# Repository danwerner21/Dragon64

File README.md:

(note that I need to get a better picture of the screen, this is s-video and is very clear in person)

# Dragon 64 Clone PCB

The Dragon 64 is a home computer that was built in the 1980s for the European market by Dragon Data, Ltd. The Dragons are very similar to the TRS-80 Color Computer, and in fact provisions have been made to allow the keyboard to become compatible with a TRS-80 color computer clone.   This version of the Dragon 64 computer produces NTSC rather than PAL composite video and has the ability to produce "Commodore style LCA" s-video output for a much clearer video display.  It also supports either a vertical or horizontal cartridge slot and TTL level serial capabilities for convenient use of modern TTL to USB adaptors.

It should be possible for this PCB to become a Tandy Color Computer clone as well, but this is not implimented in V1.

A regulated 12V and 5V power supply is required.

The main PCB also includes a DragonDOS floppy controller that can be optionally populated to support floppy disk support.

A design is included for a 3d-printed retro style case.

Note that much of this work is based on the work done by Ciaran Anscomb.  Without that original work, this would have taken much longer to complete.

More generalized information on this line of retro computers can be found here:

   * https://en.wikipedia.org/wiki/Dragon_32/64
   * https://colorcomputerarchive.com/
   * https://cococentral.com/
   * https://www.6809.org.uk/dragon/
   * http://dragondata.co.uk/

---

## To Do:
* test the joystick interface
* test the cassette interface
* test the printer interface
---

## What is included in this repo?
As of this time, the repo includes

1. The Mainboard PCB Kicad design and Gerber files
2. The Keyboard PCB Kicad design and Gerber files
3. OpenSCAD and STL files for a 3d printed case
4. SVG file for custom keycaps from MAX Keyboard

---

## Known Bugs

### System Jumpers
LK1 - Ram Size Selection 64K=1&2, 32K=2&3

J3 - Composite on Luma J3 on for composite video, off for S-video

J5 - Enable Disk ROM

---

## Bill Of Materials

### Mainboard
QTY|ref|value|part|description
--------|--------|----|--------|--------
1|IC4|4050|4050|
1|IC7|4069|4069|Hex inverter
8|IC15, IC16, IC21, IC22, IC26, IC27, IC32, IC33|4164|4164|
1|IC6|4529|4529|
1|IC11|6551|6551|
2|IC5,IC8|6821|6821|Peripheral Interface Adapter 1MHz| DIP-40
1|IC10|6847|6847|
1|IC39|6883|6883|
1|D8|1N914|1N914|100V 0.3A Small Signal Fast Switching Diode| DO-35
2|IC34,IC37|27C128|27C128|OTP EPROM 128 KiBit| [Obsolete 2004-01]
1|U5|27C64|27C64|OTP EPROM 64 KiBit| [Obsolete 2004-01]
2|IC35,U3|74LS00|74LS00|quad 2-input NAND gate
1|IC36|74LS02|74LS02|quad 2-input NOR gate
1|U6|74LS04|74LS04|Hex Inverter
1|U8|74LS06N|74LS06N|Inverter Open Collect
1|U4|74LS07|74LS07|Hex Buffers and Drivers With Open Collector High Voltage Outputs
1|IC40|74LS138|74LS138|Decoder 3 to 8 active low outputs
1|U7|74LS139|74LS139|Dual Decoder 1 of 4| Active low outputs
1|U9|74LS174|74LS174|Hex D-type Flip-Flop| reset
2|IC1|,C25|74LS244|74LS244|Octal Buffer and Line Driver With 3-State Output| active-low enables| non-inverting outputs
1|IC20|74LS273|74LS273|8-bit D Flip-Flop| reset
1|J1|Screw Terminal|5mm pitch|Power supply
1|C3|.002u|C|Unpolarized capacitor
37|C1, C7, C11, C12, C18, C20, C21, C22, C29, C31, C32, C34, C38, C39, C40, C41, C42, C43, C45, C46, C47, C50, C51, C52, C53, C55, C56, C57, C62, C65, C66, C70, C71, C72, C73, C74, C75, C76|.01u|C|Unpolarized capacitor
5|C6,C13,C14,C15,C16|.02u|C|Unpolarized capacitor
7|C27, C33, C4, C49, C59, C60, C61|.1u|C|Unpolarized capacitor
2|C33,C49|0.1uf|C|Unpolarized capacitor
1|C2|0.22uf|C|Unpolarized capacitor
1|C37|100pf|C|Unpolarized capacitor
1|C78|10nf|C|Unpolarized capacitor
2|C8,C48|1u|C|Unpolarized capacitor
1|C17|22p|C|Unpolarized capacitor
1|C35|25uf|C|Unpolarized capacitor
1|C44|470pf|C|Unpolarized capacitor
1|C67|47p|C|Unpolarized capacitor
1|C30|56pf|C|Unpolarized capacitor
1|C10|10u|C_Polarized_Small_US|Polarized capacitor| small US symbol
4|C9,C24,C25,C54|1u|C_Polarized_Small_US|Polarized capacitor| small US symbol
1|C26|C63|100uf|C_Polarized_US|Polarized capacitor| US symbol
1|C19|10uf|C_Polarized_US|Polarized capacitor| US symbol
1|C23|10uf 16v|C_Polarized_US|Polarized capacitor| US symbol
2|C58,C64|4.7uf|C_Polarized_US|Polarized capacitor| US symbol
1|C36|47uf|C_Polarized_US|Polarized capacitor| US symbol
2|C11,C7|.01u|C_Small|Unpolarized capacitor| small symbol
1|C77|8-70pf|C_Trim|Trimmable capacitor
1|J3|composite on luma|Conn_01x02_Male|Generic connector| single row| 01x02| script generated (kicad-library-utils/schlib/autogen/connector/)
1|J5|DISK ROM ENABLE|Conn_01x02_Male|Generic connector| single row| 01x02| script generated (kicad-library-utils/schlib/autogen/connector/)
1|J2|TTL Serial Connector|Conn_01x06_Male|Generic connector| single row| 01x06| script generated (kicad-library-utils/schlib/autogen/connector/)
1|PL6|Power/Video|Conn_01x09|Generic connector| single row| 01x09| script generated (kicad-library-utils/schlib/autogen/connector/)
1|PL1|Keyboard|Conn_01x16|Generic connector| single row| 01x16| script generated (kicad-library-utils/schlib/autogen/connector/)
1|PL2|Printer|Conn_02x10_Odd_Even|Generic connector| double row| 02x10| odd/even pin numbering scheme (row 1 odd numbers| row 2 even numbers)| script generated (kicad-library-utils/schlib/autogen/connector/)
1|J6|Floppy Interface|Conn_02x17_Odd_Even|Generic connector| double row| 02x17| odd/even pin numbering scheme (row 1 odd numbers| row 2 even numbers)| script generated (kicad-library-utils/schlib/autogen/connector/)
1|PL7|Cartridge|Conn_02x20_Odd_Even|Generic connector| double row| 02x20| odd/even pin numbering scheme (row 1 odd numbers| row 2 even numbers)| script generated (kicad-library-utils/schlib/autogen/connector/)
1|Y2|1.8432Mhz|Crystal|Two pin crystal
1|X1|14.31818Mhz|CXO_DIP14|Crystal Clock Oscillator| DIP14-style metal package
1|D4|1N4002|D|Diode
4|D5,D6,D7,D11|1N4148|D|Diode
4|D1,D12,D13,D14|1N914|D|Diode
2|D2,D3|BZX 61|D_Zener_Small|Zener diode| small symbol
1|J4|DB9_Male|DB9_Male|9-pin male D-SUB connector
1|PL4|Cassette|DIN-5_180degree|5-pin DIN connector (5-pin DIN-5 stereo)
2|PL3,PL5|Joystick L|DIN-6|6-pin DIN connector
1|LK1|Jumper_3_Bridged12| pins 1+2 closed/bridged
4|L1,L2,L3,L4|3.3u|L|Inductor
1|IC2|LM393|LM393|Low-Power| Low-Offset Voltage| Dual Comparators| DIP-8/SOIC-8/TO-99-8
1|U1|MAX232|MAX232|Dual RS232 driver/receiver| 5V supply| 120kb/s| 0C-70C
1|U2|MC1372|MC1372|
1|IC38|MC6809E|MC6809E|
2|Q2,Q3|2N2222|Q_NPN_BCE|NPN transistor| base/collector/emitter
1|TR1|BC182L|Q_NPN_BCE|NPN transistor| base/collector/emitter
1|Q1|BC557|Q_PNP_BCE|PNP transistor| base/collector/emitter
4|R45,R46,R47,R48|150|R|Resistor
2|R7,R12|390|R|Resistor
1|R30|420|R|Resistor
3|R6,R31,R85|470|R|Resistor
1|R43|750|R|Resistor
1|R13|820|R|Resistor
3|R17,R32,R42|100K|R|Resistor
1|R1|100R|R|Resistor
6|R9,R11,R15,R16,R26,R28|10K|R|Resistor
1|R29|10M|R|Resistor
1|R23|15K|R|Resistor
6|R10,R18,R27,R41,R44,R64|1K|R|Resistor
1|R22|1M5|R|Resistor
1|R4|220R|R|Resistor
11|R73,R74,R75,R76,R77 ,R78,R79,R80,R81,R82,R83|22R|R|Resistor
1|R40|33K|R|Resistor
1|R3|470R|R|Resistor
11|R14,R2,R24,R25,R65 ,R66,R67,R68,R69,R70,R71|4K7|R|Resistor
1|R8|5.6k|R|Resistor
2|R20,R21|56K|R|Resistor
1|R39|68K|R|Resistor
1|R19|6K8|R|Resistor
1|R5|8K2|R|Resistor
2|RV1,RV2|10K-Read|R_Potentiometer_Trim|Trim-potentiometer
1|R38|10K 1%|R_Small|Resistor| small symbol
1|R33|160K|R_Small|Resistor| small symbol
1|R37|20K 1%|R_Small|Resistor| small symbol
1|R34|330K|R_Small|Resistor| small symbol
1|R36|40K2 1%|R_Small|Resistor| small symbol
1|R35|80K6 1%|R_Small|Resistor| small symbol
1|RLA1|SPDT|TIANBO-HJR-4102-L|TIANBO HJR-4102-L| Single Pole Relay| 5mm Pitch| 3A
1|U10|WD2797|WD2797|Floppy disk controller| DIP-40
1|X2|1Mhz|XO91|HCMOS Clock Oscillator

### Keyboard
QTY|ref|value|part|description
--------|--------|----|--------|--------
53|SW(X)|KEYSWITCH|MX Cherry - Linear
3||Switch Leveling Kit|LEVELING KIT FOR LARGER KEYS|EXAMPLE:https://www.amazon.com/Keyboard-Screw-Stabilizers-6-25u-Mechanical/dp/B094R45K8Z  -or-   https://www.amazon.com/dp/B0978PWJG9 
1||Switch Leveling Kit|LEVELING KIT FOR SPACEBAR| EXAMPLE:https://www.amazon.com/Keyboard-Screw-Stabilizers-6-25u-Mechanical/dp/B094R45K8Z  -or-   https://www.amazon.com/dp/B0978PWJG9 
2|J1,J2|01X16 HEADER|Connector_PinHeader_2.54mm:PinHeader_1x16_P2.54mm_Vertical

### Floppy Drive Calibration (an oscilloscope is required)
1. power on, allow machine to reset and boot

2. ground Pin 22 of U10(WD2797)

3. Set VC0 by Measuring at pin 16 of the U10(WD2797),  Adjust the signal to 250 KHz (capacitor C77)

4. WP setting by Measuring signal at pin 31 of the U10(WD2797), Set pulse width to 300ns (RV2 potentiometer)

5. PR adjustment by Measuring signal at pin 29 of U10(WD2797), Set pulse width to 600ns (potentiometer RV1)

6. remove Pin 22 of the U10(WD2797) from ground

7. restart machine

### Case

### Questions?

If there are any questions, I can be reached at vic2020Dan at gmail dot com.

---

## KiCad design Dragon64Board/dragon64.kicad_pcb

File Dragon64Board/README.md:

# Dragon 64 schematic

... and PCB layout, in [KiCad](https://www.kicad.org/).

The schematic capture is complete, and I've done one full verification pass.
But I'm still making no promises about correctness!  I've uploaded a PDF for
those without access to KiCad.

 * [Dragon 64 schematic PDF](https://www.6809.org.uk/dragon/dragon64-schematic.pdf)

A lot of the PCB positioning is now correct - at least to the nearest mm,
usually better - and everything's pointing in a sensible direction with the
exception of some diodes: Dragon Data ensured they always had the cathode to
the right, presumably to avoid manufacturing confusion, and I've preserved that
decision.

As it stands the PCB is now fully routed.  I think it has reasonable power
distribution, and where possible, I've tried to route such that the decoupling
capacitor positions make sense.  Crystal tracks should be reasonably well
separated from anything else, and apart from a tiny skirt around the outside of
the ACIA crystal housing, no tracks pass underneath them either.

[Freerouting](https://github.com/freerouting/freerouting) did the rest, and it
looks ok to me!  Less than 200 vias in the end.  Fully autorouted achieves a
lot less, but I wasn't terribly happy with how it dealt with the sensitive bits
above.  I think 200 still compares pretty well to the original boards.

It would be nice to learn some FreeCAD to make the 3D view nicer, but
I must admit that's looking pretty low priority for now.

 * [3D view](https://www.6809.org.uk/dragon/dragon64-kicad-pcb.jpg)

Changes from the original:

 * The 240° 5-pin DIN sockets used for joysticks appear to be a bit harder to
   find now.  I've replaced them with (compatible) 6-pin sockets.
 * The footprint for the 7-pin DIN serial connector is incompatible (2-3-2
   instead of 3-4).  This reflects what I've found to be available today.
 * Two more inductors and capacitors have been added as optional components to
   enable the second firebutton on CoCo 3 compatible joysticks.

Note also that the mounting holes for the edge connector are placed
differently, and not very well with respect to the board, so definitely don't
use this layout as-is.  40-way 2.54mm pitch card edge connector sockets seem to
be like hen's teeth at the moment.  Stewart Orchard points out that EDAC list
some, and that's the footprint you currently see.  Not that anyone appears to
sell it.  Likely I'll update the footprint to match what's in our Dragons so
that if anyone's fool enough to get a board made, they can take a donor.

## Acknowledgements

Thanks to Richard Harding for hosting high quality copies of the original
drawings - doing this from the old scans would have been nigh on impossible.

 * [Original drawings](http://dragondata.co.uk/tech/circuit-diag/index.html)

Thanks also to Stewart Orchard, who has done a similar capture of the Dragon's
PSU board.  I also nabbed his 3D model of the DIN socket to represent all the
similar ports in this project (you'll notice they're the wrong shape for the
joystick ports, and none of them have more than three pins).

 * [DragonISS4PSU](https://gitlab.com/sorchard001/dragoniss4psu)

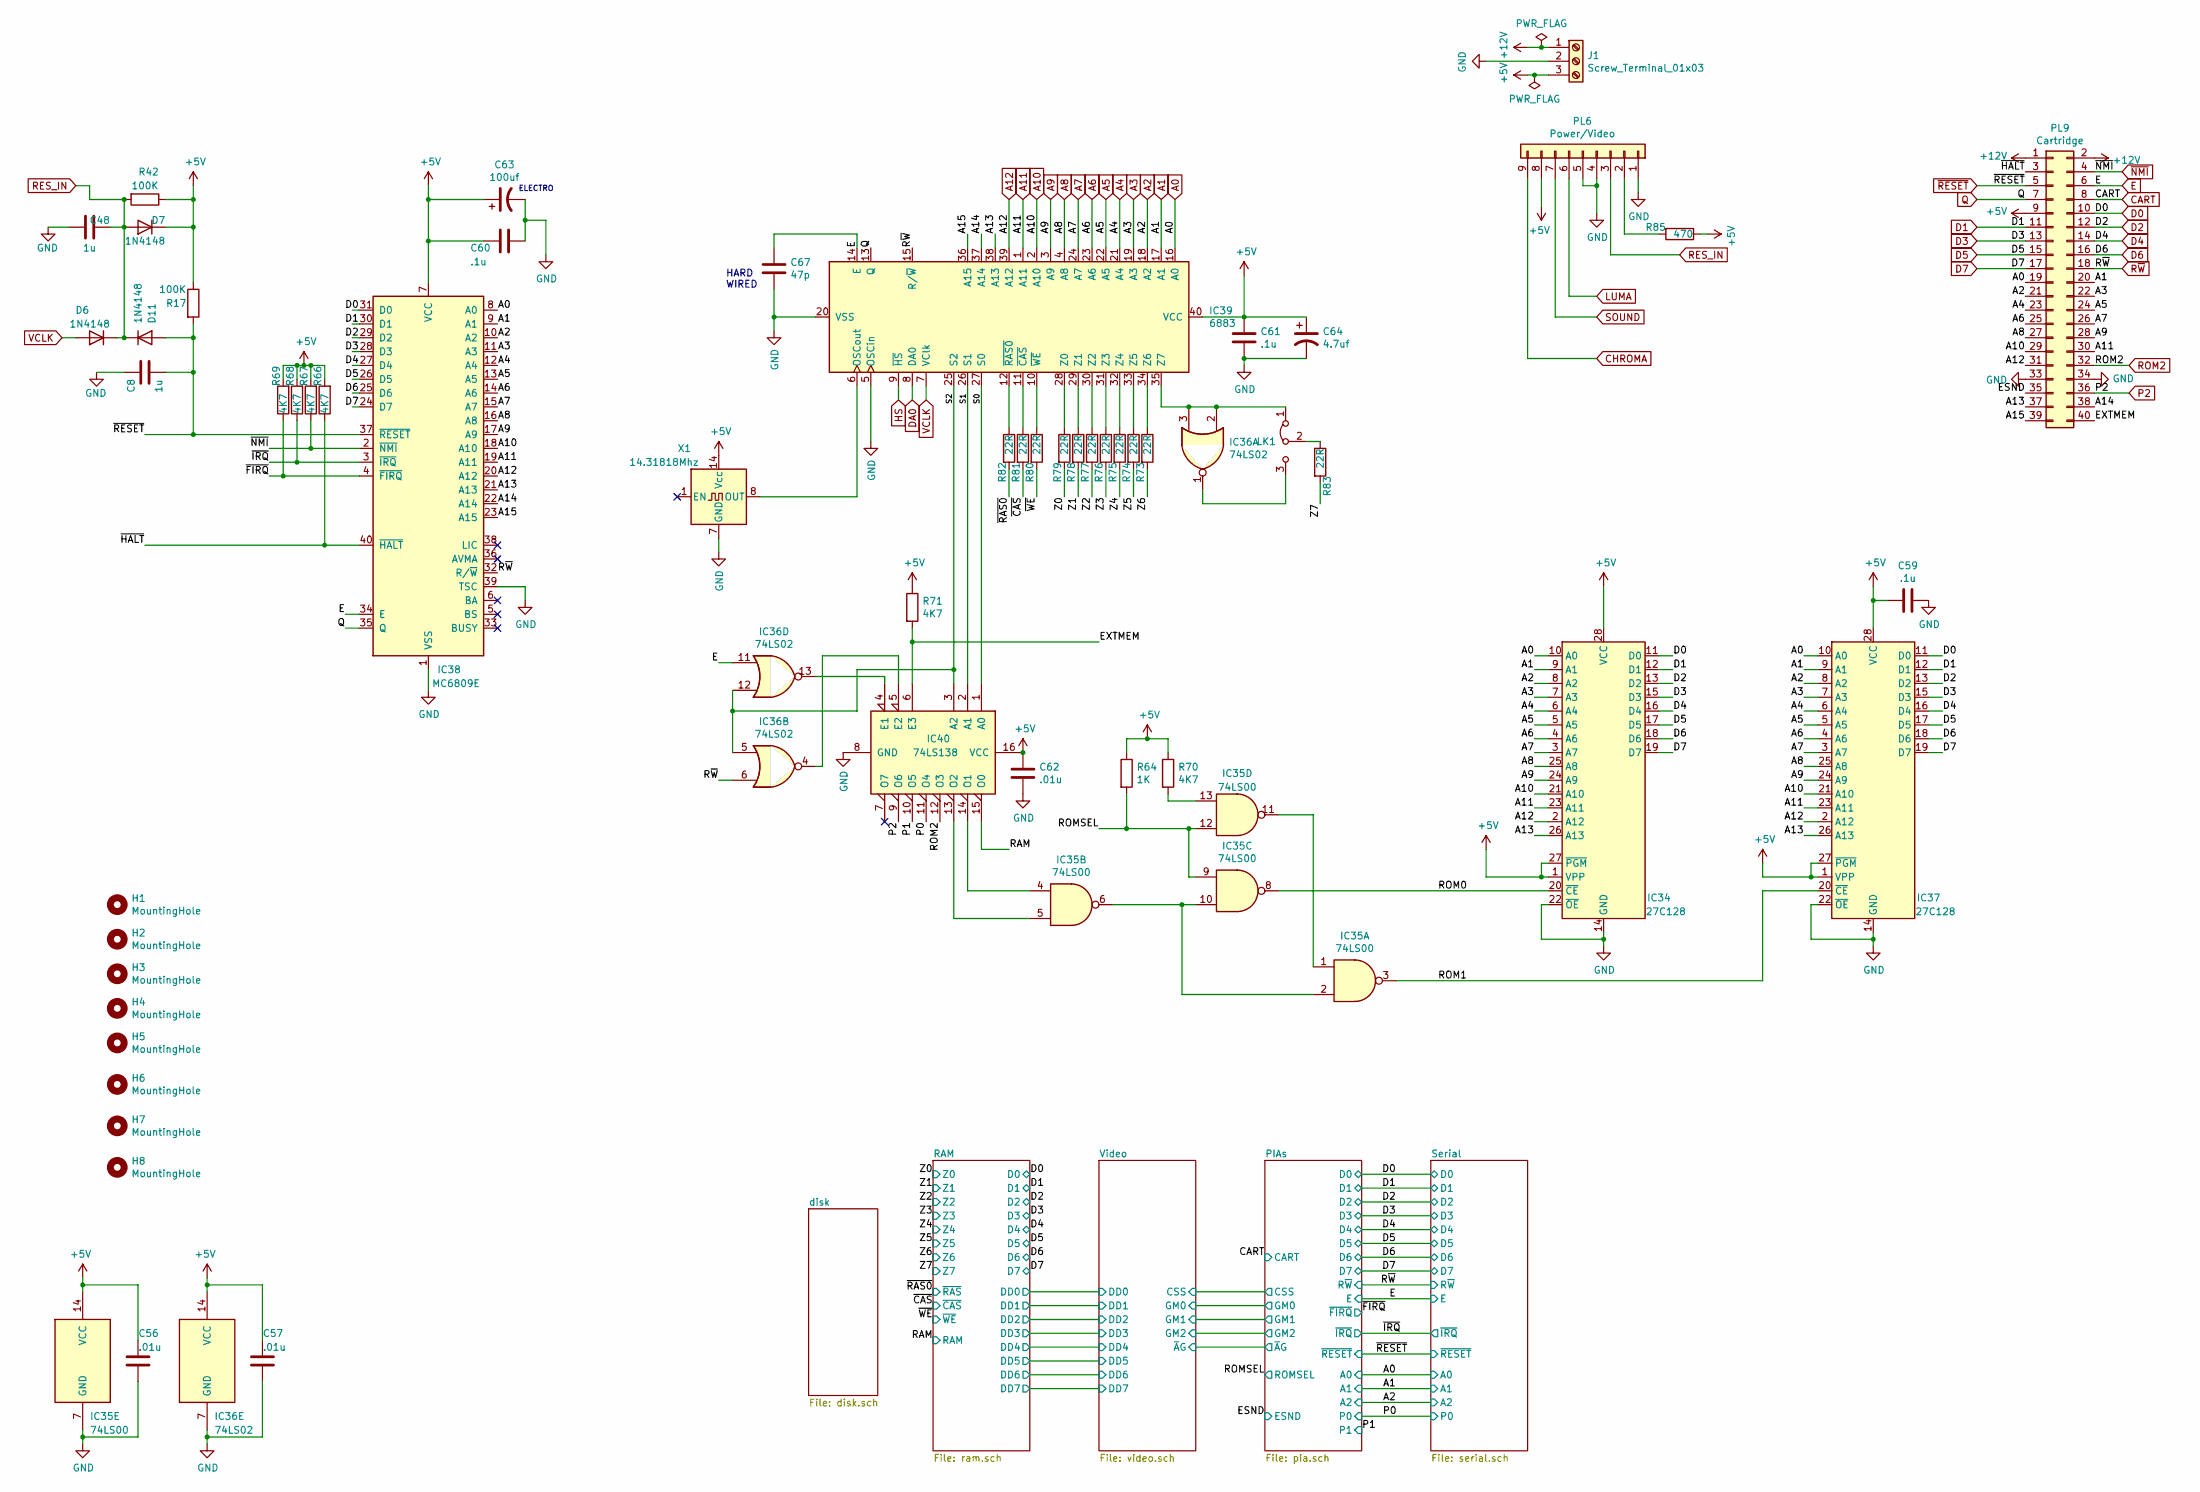
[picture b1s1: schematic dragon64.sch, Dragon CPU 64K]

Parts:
C8, C48: 1u; C_Disc_D7.5mm_W2.5mm_P5.00mm
C56, C57, C62: .01u; C_Disc_D7.5mm_W2.5mm_P5.00mm
C59, C60, C61: .1u; C_Disc_D7.5mm_W2.5mm_P5.00mm
C63: 100uf; CP_Radial_D4.0mm_P2.00mm
C64: 4.7uf; CP_Radial_D4.0mm_P2.00mm
C67: 47p; C_Disc_D7.5mm_W2.5mm_P5.00mm
D6, D7, D11: 1N4148; D_DO-35_SOD27_P7.62mm_Horizontal
H1, H2, H3, H4, H5, H6, H7, H8: MountingHole; MountingHole_3.2mm_M3
IC34, IC37: 27C128; DIP-28_W15.24mm_Socket_LongPads
IC35: 74LS00; DIP-14_W7.62mm_Socket_LongPads
IC36: 74LS02; DIP-14_W7.62mm_Socket_LongPads
IC38: MC6809E; DIP-40_W15.24mm_Socket_LongPads
IC39: 6883; DIP-40_W15.24mm_Socket_LongPads
IC40: 74LS138; DIP-16_W7.62mm_Socket_LongPads
J1: Screw_Terminal_01x03; TerminalBlock_RND_205-00277_1x03_P5.00mm_Vertical
LK1: PinHeader_1x03_P2.54mm_Vertical
PL6: Power/Video; PinHeader_1x09_P2.54mm_Vertical
PL9: Cartridge; Edge_2x20_P2.54mm_Horizontal
R17, R42: 100K; R_Axial_DIN0207_L6.3mm_D2.5mm_P7.62mm_Horizontal
R64: 1K; R_Axial_DIN0207_L6.3mm_D2.5mm_P7.62mm_Horizontal
R66, R67, R68, R69, R70, R71: 4K7; R_Axial_DIN0207_L6.3mm_D2.5mm_P7.62mm_Horizontal
R73, R74, R75, R76, R77, R78, R79, R80, R81, R82, R83: 22R; R_Axial_DIN0207_L6.3mm_D2.5mm_P7.62mm_Horizontal
R85: 470; R_Axial_DIN0207_L6.3mm_D2.5mm_P7.62mm_Horizontal
X1: 14.31818Mhz; DIP-14_W7.62mm_Socket_LongPads

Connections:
+5V: C56.1, C57.1, C59.2, C60.2, C61.2, C62.1, C63.1, C64.1, D7.1 (K), IC34.1 (VPP), IC34.27 (~PGM), IC34.28 (VCC), IC35.14 (VCC), IC36.14 (VCC), IC37.1 (VPP), IC37.27 (~PGM), IC37.28 (VCC), IC38.7 (VCC), IC39.40 (VCC), IC40.16 (VCC), J1.3, PL6.8, PL9.9, R17.1, R42.1, R64.1, R66.2, R67.2, R68.2, R69.2, R70.1, R71.1, R85.1, X1.14 (Vcc); also elsewhere on the board
+12V: J1.1, PL9.1, PL9.2; also elsewhere on the board
/A13: IC34.26 (A13), IC37.26 (A13), IC38.21 (A13), IC39.38 (A13), PL9.37
/A14: IC38.22 (A14), IC39.37 (A14), PL9.38
/A15: IC38.23 (A15), IC39.36 (A15), PL9.39
/ESND: PL9.35; also elsewhere on the board
/EXTMEM: IC40.6 (E3), PL9.40, R71.2
/P0: IC40.11 (O4); also elsewhere on the board
/P1: IC40.10 (O5); also elsewhere on the board
/RAM: IC40.15 (O0); also elsewhere on the board
/ROM0: IC34.20 (~CE), IC35.8
/ROM1: IC35.3, IC37.20 (~CE)
/ROMSEL: IC35.9, IC35.12, R64.2; also elsewhere on the board
/S0: IC39.27 (S0), IC40.1 (A0)
/S1: IC39.26 (S1), IC40.2 (A1)
/S2: IC36.5, IC36.12, IC39.25 (S2), IC40.3 (A2)
/Z0: R79.2; also elsewhere on the board
/Z1: R78.2; also elsewhere on the board
/Z2: R77.2; also elsewhere on the board
/Z3: R76.2; also elsewhere on the board
/Z4: R75.2; also elsewhere on the board
/Z5: R74.2; also elsewhere on the board
/Z6: R73.2; also elsewhere on the board
/Z7: R83.2; also elsewhere on the board
/~CAS: R81.2; also elsewhere on the board
/~FIRQ: IC38.4 (~FIRQ), R69.1; also elsewhere on the board
/~HALT: IC38.40 (~HALT), PL9.3, R66.1
/~IRQ: IC38.3 (~IRQ), R68.1; also elsewhere on the board
/~RAS0: R82.2; also elsewhere on the board
/~WE: R80.2; also elsewhere on the board
A0: IC34.10 (A0), IC37.10 (A0), IC38.8 (A0), IC39.16 (A0), PL9.19; also elsewhere on the board
A1: IC34.9 (A1), IC37.9 (A1), IC38.9 (A1), IC39.17 (A1), PL9.20; also elsewhere on the board
A2: IC34.8 (A2), IC37.8 (A2), IC38.10 (A2), IC39.18 (A2), PL9.21; also elsewhere on the board
A3: IC34.7 (A3), IC37.7 (A3), IC38.11 (A3), IC39.19 (A3), PL9.22; also elsewhere on the board
A4: IC34.6 (A4), IC37.6 (A4), IC38.12 (A4), IC39.21 (A4), PL9.23; also elsewhere on the board
A5: IC34.5 (A5), IC37.5 (A5), IC38.13 (A5), IC39.22 (A5), PL9.24; also elsewhere on the board
A6: IC34.4 (A6), IC37.4 (A6), IC38.14 (A6), IC39.23 (A6), PL9.25; also elsewhere on the board
A7: IC34.3 (A7), IC37.3 (A7), IC38.15 (A7), IC39.24 (A7), PL9.26; also elsewhere on the board
A8: IC34.25 (A8), IC37.25 (A8), IC38.16 (A8), IC39.4 (A8), PL9.27; also elsewhere on the board
A9: IC34.24 (A9), IC37.24 (A9), IC38.17 (A9), IC39.3 (A9), PL9.28; also elsewhere on the board
A10: IC34.21 (A10), IC37.21 (A10), IC38.18 (A10), IC39.2 (A10), PL9.29; also elsewhere on the board
A11: IC34.23 (A11), IC37.23 (A11), IC38.19 (A11), IC39.1 (A11), PL9.30; also elsewhere on the board
A12: IC34.2 (A12), IC37.2 (A12), IC38.20 (A12), IC39.39 (A12), PL9.31; also elsewhere on the board
CART: PL9.8; also elsewhere on the board
CHROMA: PL6.9; also elsewhere on the board
D0: IC34.11 (D0), IC37.11 (D0), IC38.31 (D0), PL9.10; also elsewhere on the board
D1: IC34.12 (D1), IC37.12 (D1), IC38.30 (D1), PL9.11; also elsewhere on the board
D2: IC34.13 (D2), IC37.13 (D2), IC38.29 (D2), PL9.12; also elsewhere on the board
D3: IC34.15 (D3), IC37.15 (D3), IC38.28 (D3), PL9.13; also elsewhere on the board
D4: IC34.16 (D4), IC37.16 (D4), IC38.27 (D4), PL9.14; also elsewhere on the board
D5: IC34.17 (D5), IC37.17 (D5), IC38.26 (D5), PL9.15; also elsewhere on the board
D6: IC34.18 (D6), IC37.18 (D6), IC38.25 (D6), PL9.16; also elsewhere on the board
D7: IC34.19 (D7), IC37.19 (D7), IC38.24 (D7), PL9.17; also elsewhere on the board
DA0: IC39.8 (DA0); also elsewhere on the board
E: C67.2, IC36.11, IC38.34 (E), IC39.14 (E), PL9.6; also elsewhere on the board
GND: C8.1, C48.1, C56.2, C57.2, C59.1, C60.1, C61.1, C62.2, C63.2, C64.2, C67.1, IC34.14 (GND), IC34.22 (~OE), IC35.7 (GND), IC36.7 (GND), IC37.14 (GND), IC37.22 (~OE), IC38.1 (VSS), IC38.39 (TSC), IC39.5 (OSCin), IC39.20 (VSS), IC40.8 (GND), J1.2, PL6.1, PL6.4, PL6.5, PL9.33, PL9.34, X1.7 (GND); also elsewhere on the board
HS: IC39.9 (~HS~); also elsewhere on the board
LUMA: PL6.6; also elsewhere on the board
unnamed: IC35.1, IC35.11
unnamed: IC35.4, IC40.14 (O1)
unnamed: IC35.5, IC40.13 (O2)
unnamed: IC35.2, IC35.6, IC35.10
unnamed: IC35.13, R70.2
unnamed: IC36.1, LK1.3 (B)
unnamed: IC36.2, IC36.3, IC39.35 (Z7), LK1.1 (A)
unnamed: IC36.4, IC40.5 (E2)
unnamed: IC36.13, IC40.4 (E1)
unnamed: IC39.6 (OSCout), X1.8 (OUT)
unnamed: IC39.10 (~WE~), R80.1
unnamed: IC39.11 (~CAS~), R81.1
unnamed: IC39.12 (~RAS0~), R82.1
unnamed: IC39.28 (Z0), R79.1
unnamed: IC39.29 (Z1), R78.1
unnamed: IC39.30 (Z2), R77.1
unnamed: IC39.31 (Z3), R76.1
unnamed: IC39.32 (Z4), R75.1
unnamed: IC39.33 (Z5), R74.1
unnamed: IC39.34 (Z6), R73.1
unnamed: LK1.2 (C), R83.1
unnamed: PL6.2, R85.2
P2: IC40.9 (O6), PL9.36; also elsewhere on the board
Q: IC38.35 (Q), IC39.13 (Q), PL9.7; also elsewhere on the board
RES_IN: C48.2, D6.1 (K), D7.2 (A), D11.1 (K), PL6.3, R42.2
ROM2: IC40.12 (O3), PL9.32; also elsewhere on the board
R~W~: IC36.6, IC38.32 (R/~W), IC39.15 (R/~W~), PL9.18; also elsewhere on the board
SOUND: PL6.7; also elsewhere on the board
VCLK: D6.2 (A), IC39.7 (VClk); also elsewhere on the board
~NMI: IC38.2 (~NMI), PL9.4, R67.1; also elsewhere on the board
~RESET: C8.2, D11.2 (A), IC38.37 (~RESET), PL9.5, R17.2; also elsewhere on the board

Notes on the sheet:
HARD WIRED
ELECTRO

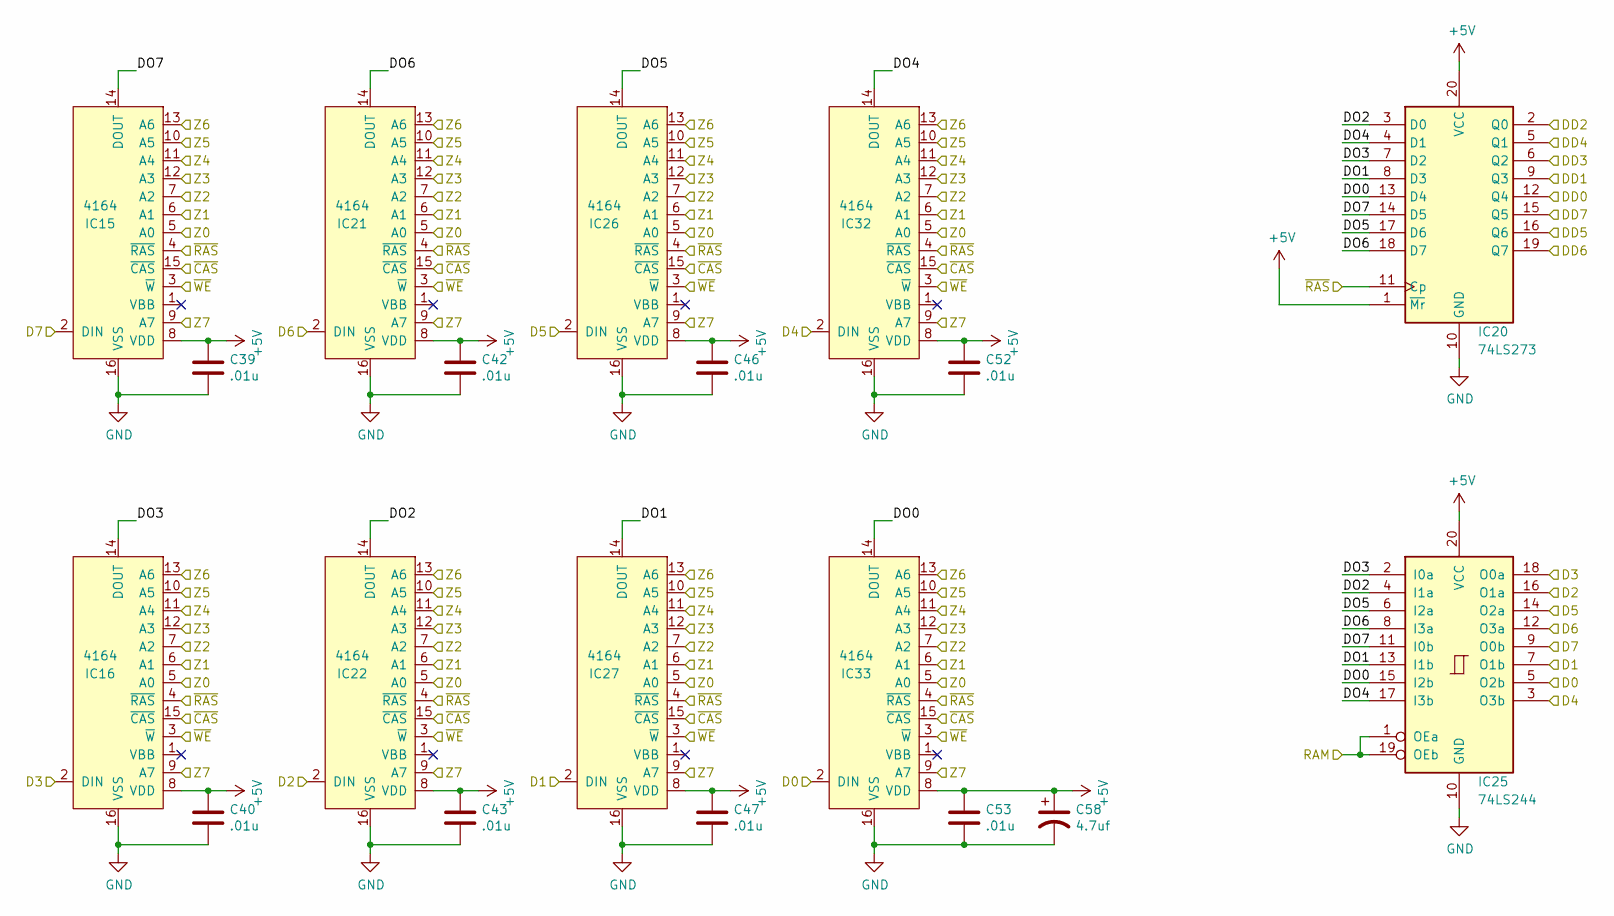
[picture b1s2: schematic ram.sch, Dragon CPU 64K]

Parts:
C39, C40, C42, C43, C46, C47, C52, C53: .01u; C_Disc_D7.5mm_W2.5mm_P5.00mm
C58: 4.7uf; CP_Radial_D4.0mm_P2.00mm
IC15, IC16, IC21, IC22, IC26, IC27, IC32, IC33: 4164; DIP-16_W7.62mm_Socket_LongPads
IC20: 74LS273; DIP-20_W7.62mm_Socket_LongPads
IC25: 74LS244; DIP-20_W7.62mm_Socket_LongPads

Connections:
+5V: C39.1, C40.1, C42.1, C43.1, C46.1, C47.1, C52.1, C53.1, C58.1, IC15.8 (VDD), IC16.8 (VDD), IC20.1 (~Mr), IC20.20 (VCC), IC21.8 (VDD), IC22.8 (VDD), IC25.20 (VCC), IC26.8 (VDD), IC27.8 (VDD), IC32.8 (VDD), IC33.8 (VDD); also elsewhere on the board
/RAM: IC25.1 (OEa), IC25.19 (OEb); also elsewhere on the board
/RAM/DD0: IC20.12 (Q4); also elsewhere on the board
/RAM/DD1: IC20.9 (Q3); also elsewhere on the board
/RAM/DD2: IC20.2 (Q0); also elsewhere on the board
/RAM/DD3: IC20.6 (Q2); also elsewhere on the board
/RAM/DD4: IC20.5 (Q1); also elsewhere on the board
/RAM/DD5: IC20.16 (Q6); also elsewhere on the board
/RAM/DD6: IC20.19 (Q7); also elsewhere on the board
/RAM/DD7: IC20.15 (Q5); also elsewhere on the board
/RAM/DO0: IC20.13 (D4), IC25.15 (I2b), IC33.14 (DOUT)
/RAM/DO1: IC20.8 (D3), IC25.13 (I1b), IC27.14 (DOUT)
/RAM/DO2: IC20.3 (D0), IC22.14 (DOUT), IC25.4 (I1a)
/RAM/DO3: IC16.14 (DOUT), IC20.7 (D2), IC25.2 (I0a)
/RAM/DO4: IC20.4 (D1), IC25.17 (I3b), IC32.14 (DOUT)
/RAM/DO5: IC20.17 (D6), IC25.6 (I2a), IC26.14 (DOUT)
/RAM/DO6: IC20.18 (D7), IC21.14 (DOUT), IC25.8 (I3a)
/RAM/DO7: IC15.14 (DOUT), IC20.14 (D5), IC25.11 (I0b)
/Z0: IC15.5 (A0), IC16.5 (A0), IC21.5 (A0), IC22.5 (A0), IC26.5 (A0), IC27.5 (A0), IC32.5 (A0), IC33.5 (A0); also elsewhere on the board
/Z1: IC15.6 (A1), IC16.6 (A1), IC21.6 (A1), IC22.6 (A1), IC26.6 (A1), IC27.6 (A1), IC32.6 (A1), IC33.6 (A1); also elsewhere on the board
/Z2: IC15.7 (A2), IC16.7 (A2), IC21.7 (A2), IC22.7 (A2), IC26.7 (A2), IC27.7 (A2), IC32.7 (A2), IC33.7 (A2); also elsewhere on the board
/Z3: IC15.12 (A3), IC16.12 (A3), IC21.12 (A3), IC22.12 (A3), IC26.12 (A3), IC27.12 (A3), IC32.12 (A3), IC33.12 (A3); also elsewhere on the board
/Z4: IC15.11 (A4), IC16.11 (A4), IC21.11 (A4), IC22.11 (A4), IC26.11 (A4), IC27.11 (A4), IC32.11 (A4), IC33.11 (A4); also elsewhere on the board
/Z5: IC15.10 (A5), IC16.10 (A5), IC21.10 (A5), IC22.10 (A5), IC26.10 (A5), IC27.10 (A5), IC32.10 (A5), IC33.10 (A5); also elsewhere on the board
/Z6: IC15.13 (A6), IC16.13 (A6), IC21.13 (A6), IC22.13 (A6), IC26.13 (A6), IC27.13 (A6), IC32.13 (A6), IC33.13 (A6); also elsewhere on the board
/Z7: IC15.9 (A7), IC16.9 (A7), IC21.9 (A7), IC22.9 (A7), IC26.9 (A7), IC27.9 (A7), IC32.9 (A7), IC33.9 (A7); also elsewhere on the board
/~CAS: IC15.15 (~CAS~), IC16.15 (~CAS~), IC21.15 (~CAS~), IC22.15 (~CAS~), IC26.15 (~CAS~), IC27.15 (~CAS~), IC32.15 (~CAS~), IC33.15 (~CAS~); also elsewhere on the board
/~RAS0: IC15.4 (~RAS~), IC16.4 (~RAS~), IC20.11 (Cp), IC21.4 (~RAS~), IC22.4 (~RAS~), IC26.4 (~RAS~), IC27.4 (~RAS~), IC32.4 (~RAS~), IC33.4 (~RAS~); also elsewhere on the board
/~WE: IC15.3 (~W~), IC16.3 (~W~), IC21.3 (~W~), IC22.3 (~W~), IC26.3 (~W~), IC27.3 (~W~), IC32.3 (~W~), IC33.3 (~W~); also elsewhere on the board
D0: IC25.5 (O2b), IC33.2 (DIN); also elsewhere on the board
D1: IC25.7 (O1b), IC27.2 (DIN); also elsewhere on the board
D2: IC22.2 (DIN), IC25.16 (O1a); also elsewhere on the board
D3: IC16.2 (DIN), IC25.18 (O0a); also elsewhere on the board
D4: IC25.3 (O3b), IC32.2 (DIN); also elsewhere on the board
D5: IC25.14 (O2a), IC26.2 (DIN); also elsewhere on the board
D6: IC21.2 (DIN), IC25.12 (O3a); also elsewhere on the board
D7: IC15.2 (DIN), IC25.9 (O0b); also elsewhere on the board
GND: C39.2, C40.2, C42.2, C43.2, C46.2, C47.2, C52.2, C53.2, C58.2, IC15.16 (VSS), IC16.16 (VSS), IC20.10 (GND), IC21.16 (VSS), IC22.16 (VSS), IC25.10 (GND), IC26.16 (VSS), IC27.16 (VSS), IC32.16 (VSS), IC33.16 (VSS); also elsewhere on the board

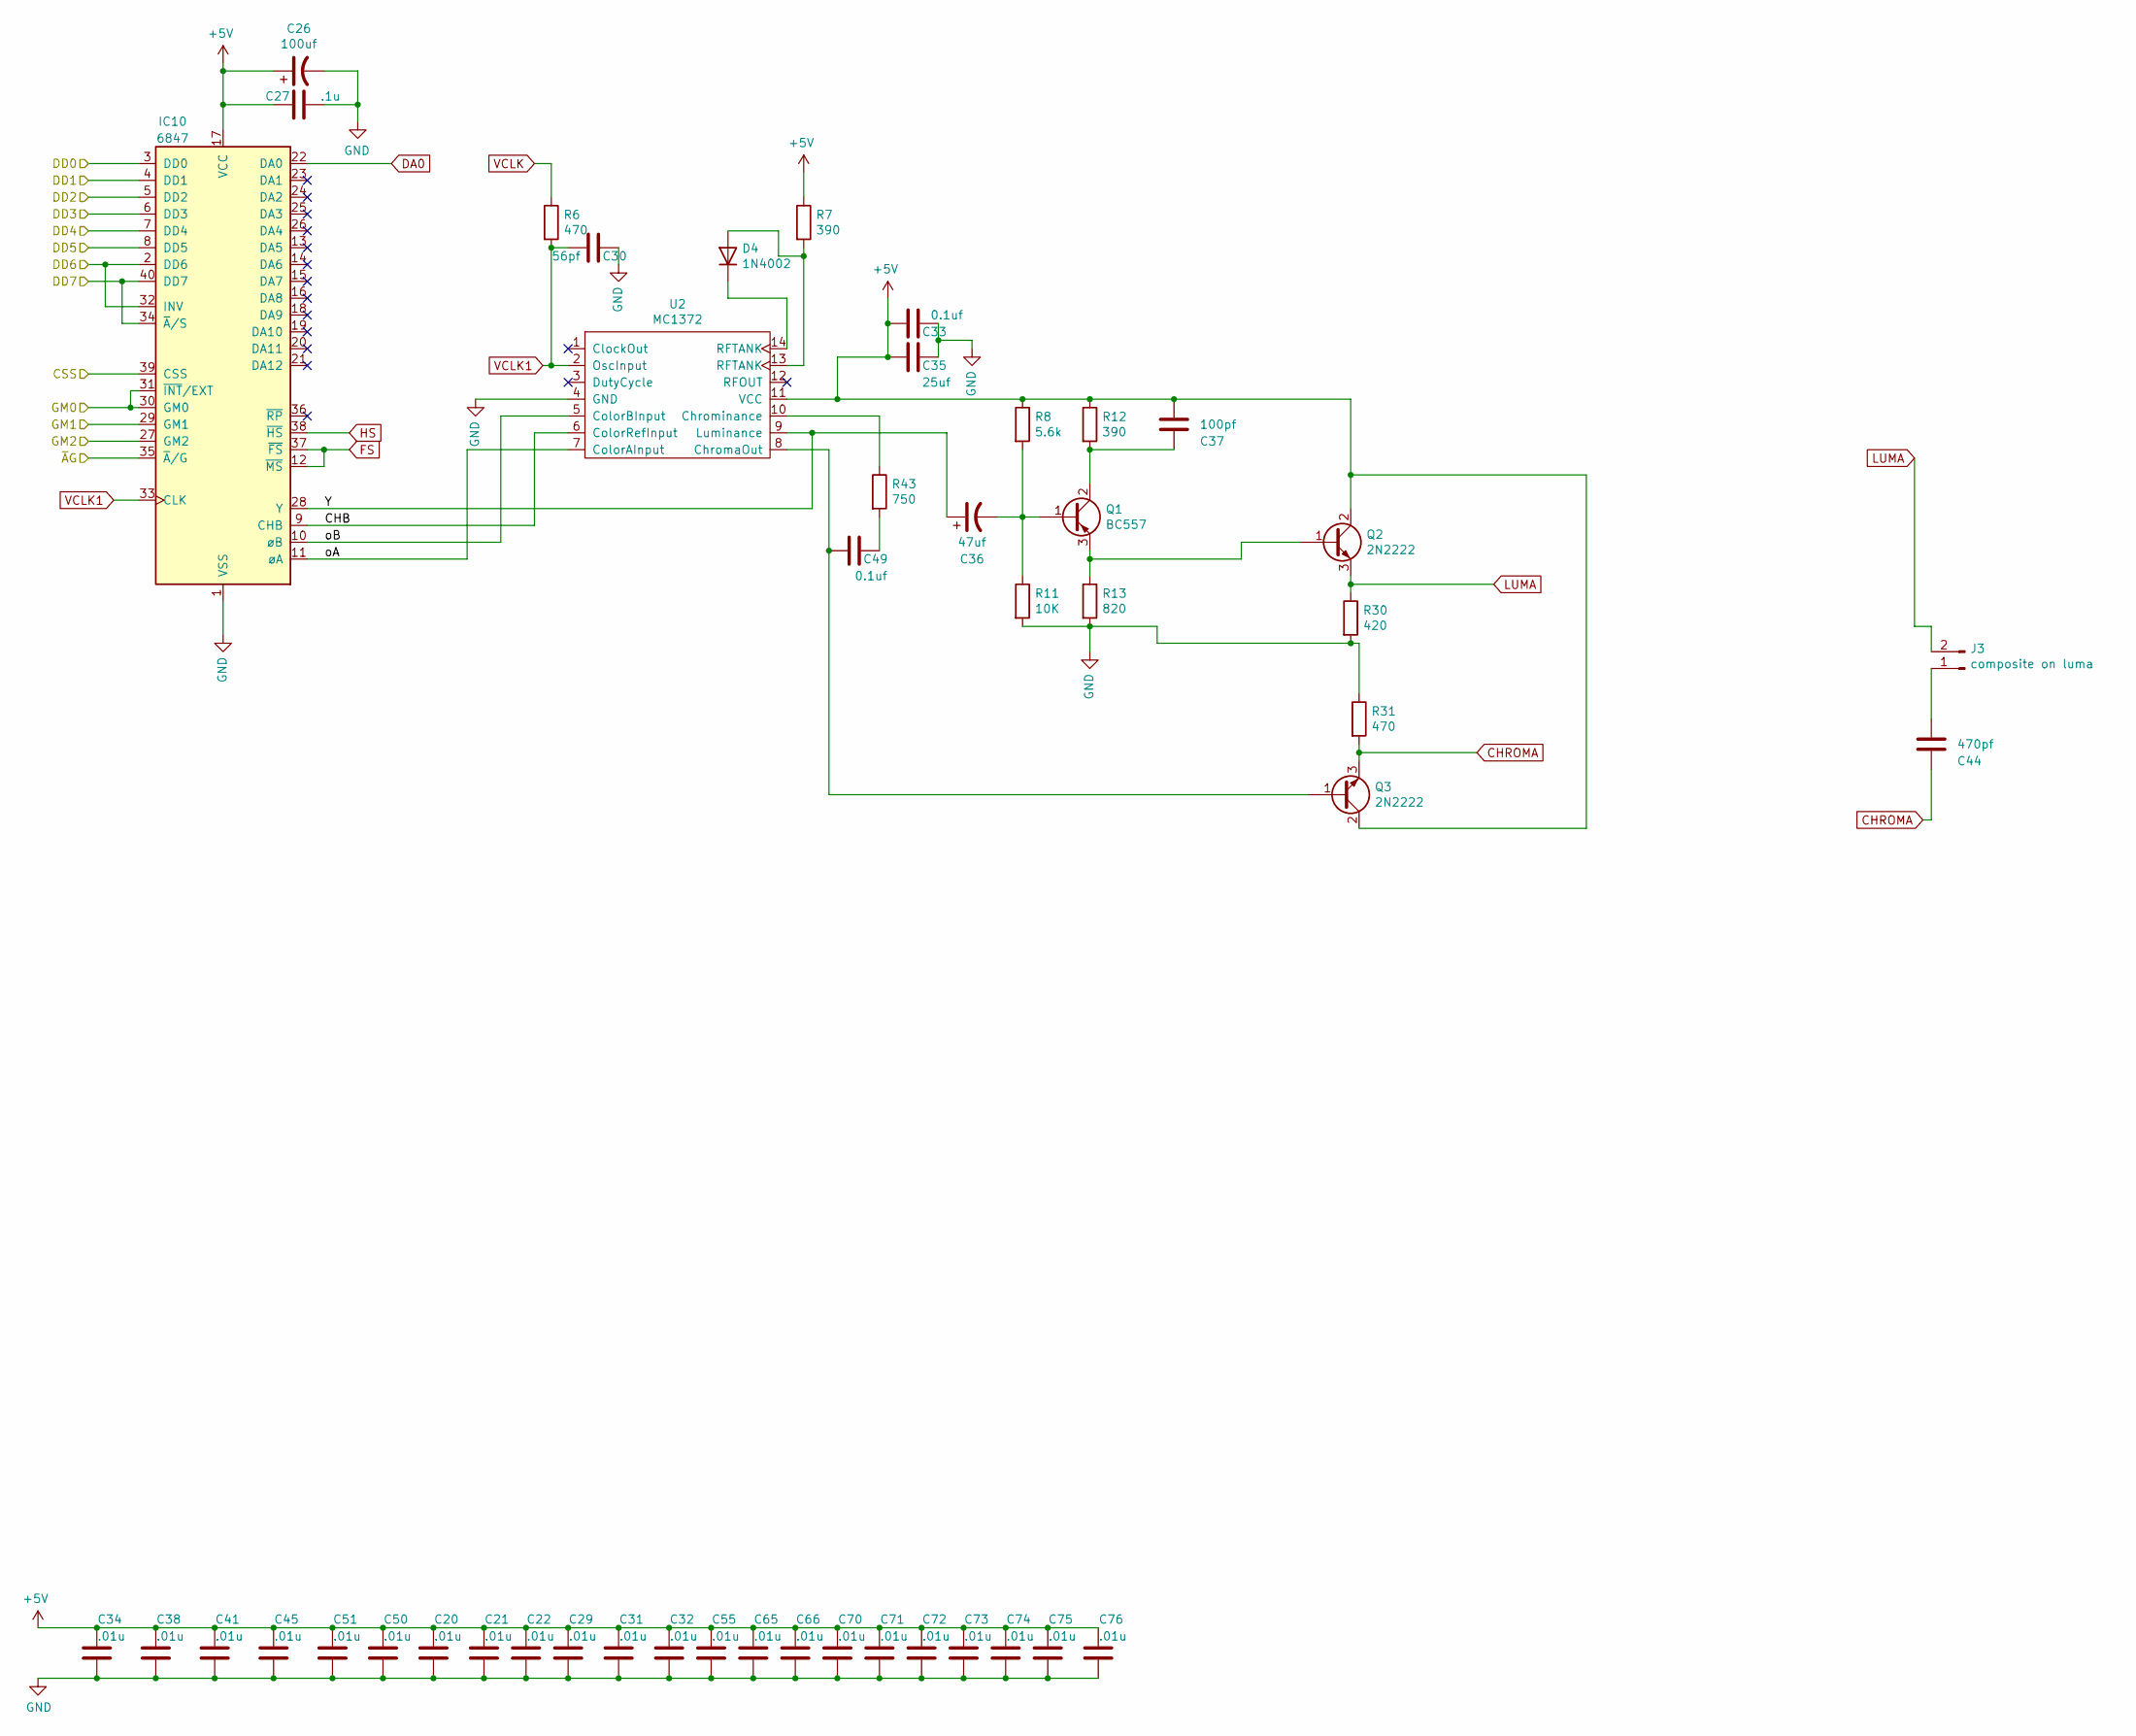
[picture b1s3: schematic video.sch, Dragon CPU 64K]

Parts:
C20, C21, C22, C29, C31, C32, C34, C38, C41, C45, C50, C51, C55, C65, C66, C70, C71, C72, C73, C74, C75, C76: .01u; C_Disc_D7.5mm_W2.5mm_P5.00mm
C26: 100uf; CP_Radial_D4.0mm_P2.00mm
C27: .1u; C_Disc_D7.5mm_W2.5mm_P5.00mm
C30: 56pf; C_Disc_D7.5mm_W2.5mm_P5.00mm
C33, C49: 0.1uf; C_Disc_D7.5mm_W2.5mm_P5.00mm
C35: 25uf; C_Disc_D7.5mm_W2.5mm_P5.00mm
C36: 47uf; CP_Radial_D4.0mm_P2.00mm
C37: 100pf; C_Disc_D7.5mm_W2.5mm_P5.00mm
C44: 470pf; C_Disc_D7.5mm_W2.5mm_P5.00mm
D4: 1N4002; D_DO-35_SOD27_P7.62mm_Horizontal
IC10: 6847; DIP-40_W15.24mm_Socket_LongPads
J3: composite on luma; PinHeader_1x02_P2.54mm_Vertical
Q1: BC557; TO-92_HandSolder_FIXED
Q2, Q3: 2N2222; TO-18-3_FIXED
R6, R31: 470; R_Axial_DIN0207_L6.3mm_D2.5mm_P7.62mm_Horizontal
R7, R12: 390; R_Axial_DIN0207_L6.3mm_D2.5mm_P7.62mm_Horizontal
R8: 5.6k; R_Axial_DIN0207_L6.3mm_D2.5mm_P7.62mm_Horizontal
R11: 10K; R_Axial_DIN0207_L6.3mm_D2.5mm_P7.62mm_Horizontal
R13: 820; R_Axial_DIN0207_L6.3mm_D2.5mm_P7.62mm_Horizontal
R30: 420; R_Axial_DIN0207_L6.3mm_D2.5mm_P7.62mm_Horizontal
R43: 750; R_Axial_DIN0207_L6.3mm_D2.5mm_P7.62mm_Horizontal
U2: MC1372; DIP-14_W7.62mm_Socket_LongPads

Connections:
+5V: C20.1, C21.1, C22.1, C26.1, C27.2, C29.1, C31.1, C32.1, C33.1, C34.1, C35.1, C37.1, C38.1, C41.1, C45.1, C50.1, C51.1, C55.1, C65.1, C66.1, C70.1, C71.1, C72.1, C73.1, C74.1, C75.1, C76.1, IC10.17 (VCC), Q2.2 (C), Q3.2 (C), R7.1, R8.1, R12.1, U2.11 (VCC); also elsewhere on the board
/PIAs/CSS: IC10.39 (CSS); also elsewhere on the board
/PIAs/GM0: IC10.30 (GM0), IC10.31 (~INT~/EXT); also elsewhere on the board
/PIAs/GM1: IC10.29 (GM1); also elsewhere on the board
/PIAs/GM2: IC10.27 (GM2); also elsewhere on the board
/PIAs/~A~G: IC10.35 (~A~/G); also elsewhere on the board
/RAM/DD0: IC10.3 (DD0); also elsewhere on the board
/RAM/DD1: IC10.4 (DD1); also elsewhere on the board
/RAM/DD2: IC10.5 (DD2); also elsewhere on the board
/RAM/DD3: IC10.6 (DD3); also elsewhere on the board
/RAM/DD4: IC10.7 (DD4); also elsewhere on the board
/RAM/DD5: IC10.8 (DD5); also elsewhere on the board
/RAM/DD6: IC10.2 (DD6), IC10.32 (INV); also elsewhere on the board
/RAM/DD7: IC10.34 (~A~/S), IC10.40 (DD7); also elsewhere on the board
/Video/CHB: IC10.9 (CHB), U2.6 (ColorRefInput)
/Video/Y: C36.1, IC10.28 (Y), U2.9 (Luminance)
/Video/oA: IC10.11 (øA), U2.7 (ColorAInput)
/Video/oB: IC10.10 (øB), U2.5 (ColorBInput)
CHROMA: C44.2, Q3.3 (E), R31.2; also elsewhere on the board
DA0: IC10.22 (DA0); also elsewhere on the board
FS: IC10.12 (~MS~), IC10.37 (~FS~); also elsewhere on the board
GND: C20.2, C21.2, C22.2, C26.2, C27.1, C29.2, C30.2, C31.2, C32.2, C33.2, C34.2, C35.2, C38.2, C41.2, C45.2, C50.2, C51.2, C55.2, C65.2, C66.2, C70.2, C71.2, C72.2, C73.2, C74.2, C75.2, C76.2, IC10.1 (VSS), R11.2, R13.2, R30.2, R31.1, U2.4 (GND); also elsewhere on the board
HS: IC10.38 (~HS~); also elsewhere on the board
LUMA: J3.2, Q2.3 (E), R30.1; also elsewhere on the board
unnamed: C36.2, Q1.1 (B), R8.2, R11.1
unnamed: C37.2, Q1.2 (C), R12.2
unnamed: C44.1, J3.1
unnamed: C49.1, Q3.1 (B), U2.8 (ChromaOut)
unnamed: C49.2, R43.2
unnamed: D4.1 (K), U2.14 (RFTANK)
unnamed: D4.2 (A), R7.2, U2.13 (RFTANK)
unnamed: Q1.3 (E), Q2.1 (B), R13.1
unnamed: R43.1, U2.10 (Chrominance)
VCLK: R6.1; also elsewhere on the board
VCLK1: C30.1, IC10.33 (CLK), R6.2, U2.2 (OscInput)
